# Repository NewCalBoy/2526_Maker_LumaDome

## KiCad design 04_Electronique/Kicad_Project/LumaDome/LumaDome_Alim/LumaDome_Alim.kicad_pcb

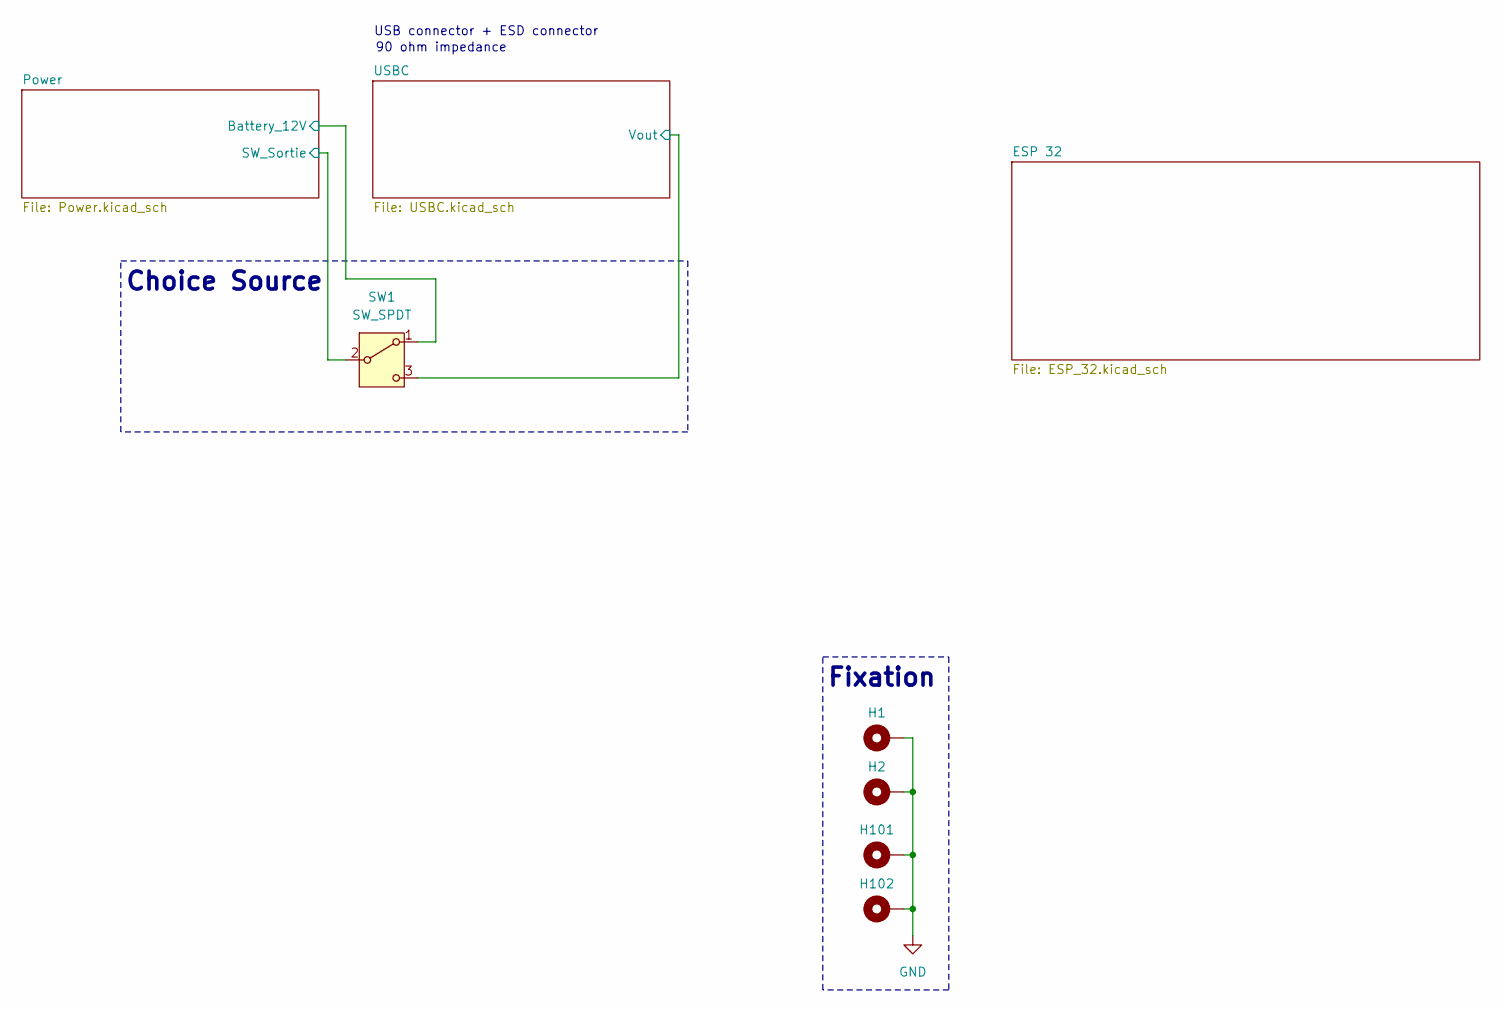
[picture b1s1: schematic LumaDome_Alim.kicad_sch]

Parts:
H1, H2, H101, H102: MountingHole_Pad; MountingHole_2.2mm_M2_Pad_Via
SW1: SW_SPDT; B12AV

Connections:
+12V: SW1.1 (A); also elsewhere on the board
/Power/SW_Sortie: SW1.2 (B); also elsewhere on the board
/USBC/Vout: SW1.3 (C); also elsewhere on the board
GND: H1.1, H2.1, H101.1, H102.1; also elsewhere on the board

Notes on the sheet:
90 ohm impedance
USB connector + ESD connector
Fixation
Choice Source

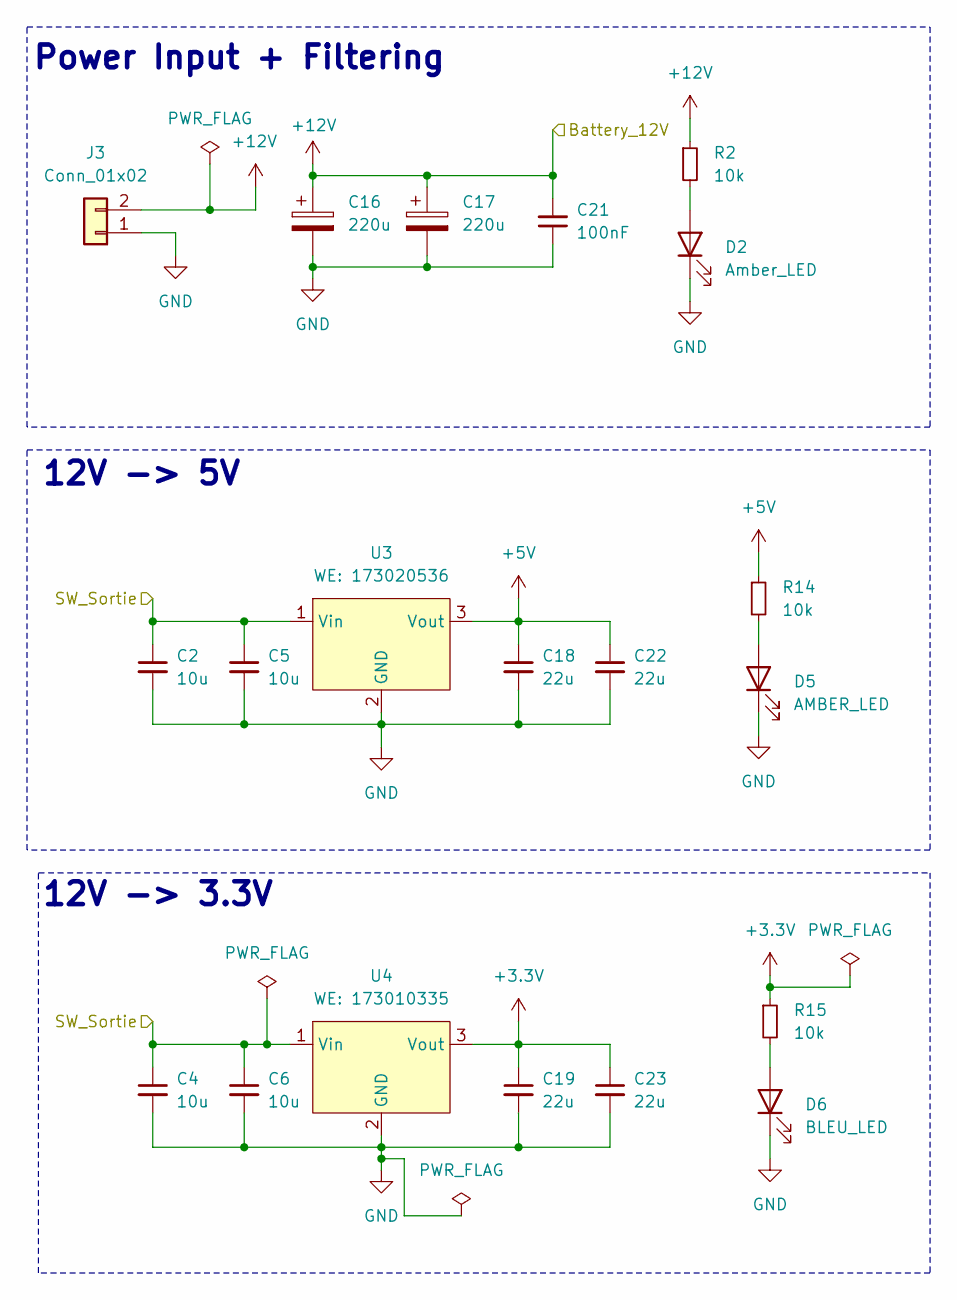
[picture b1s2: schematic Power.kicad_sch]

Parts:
C2, C4, C5, C6: 10u; C_2220_5750Metric; MPN 885012214001
C16, C17: 220u; CP_Elec_10x10.5; MPN 865060657012
C18, C19, C22, C23: 22u; C_2220_5750Metric; MPN 885012106031
C21: 100nF; C_0603_1608Metric
D2: Amber_LED; C_0603_1608Metric; MPN 150060AS55040
D5: AMBER_LED; C_0603_1608Metric; MPN 150060BS55040
D6: BLEU_LED; C_0603_1608Metric; MPN 150060BS55040
J3: Conn_01x02; AMASS_XT30UPB-F_1x02_P5.0mm_Vertical
R2, R14, R15: 10k; R_0603_1608Metric
U3: WE: 173020536; 173020536
U4: WE: 173010335; 173010335

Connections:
+3.3V: C19.1, C23.1, R15.1, U4.3 (Vout); also elsewhere on the board
+5V: C18.1, C22.1, R14.1, U3.3 (Vout); also elsewhere on the board
+12V: C16.1, C17.1, C21.2, J3.2, R2.1; also elsewhere on the board
/Power/SW_Sortie: C2.1, C4.1, C5.1, C6.1, U3.1 (Vin), U4.1 (Vin); also elsewhere on the board
GND: C2.2, C4.2, C5.2, C6.2, C16.2, C17.2, C18.2, C19.2, C21.1, C22.2, C23.2, D2.1 (K), D5.1 (K), D6.1 (K), J3.1, U3.2 (GND), U4.2 (GND); also elsewhere on the board
unnamed: D2.2 (A), R2.2
unnamed: D5.2 (A), R14.2
unnamed: D6.2 (A), R15.2

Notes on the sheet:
12V -> 5V
Power Input + Filtering
12V -> 3.3V

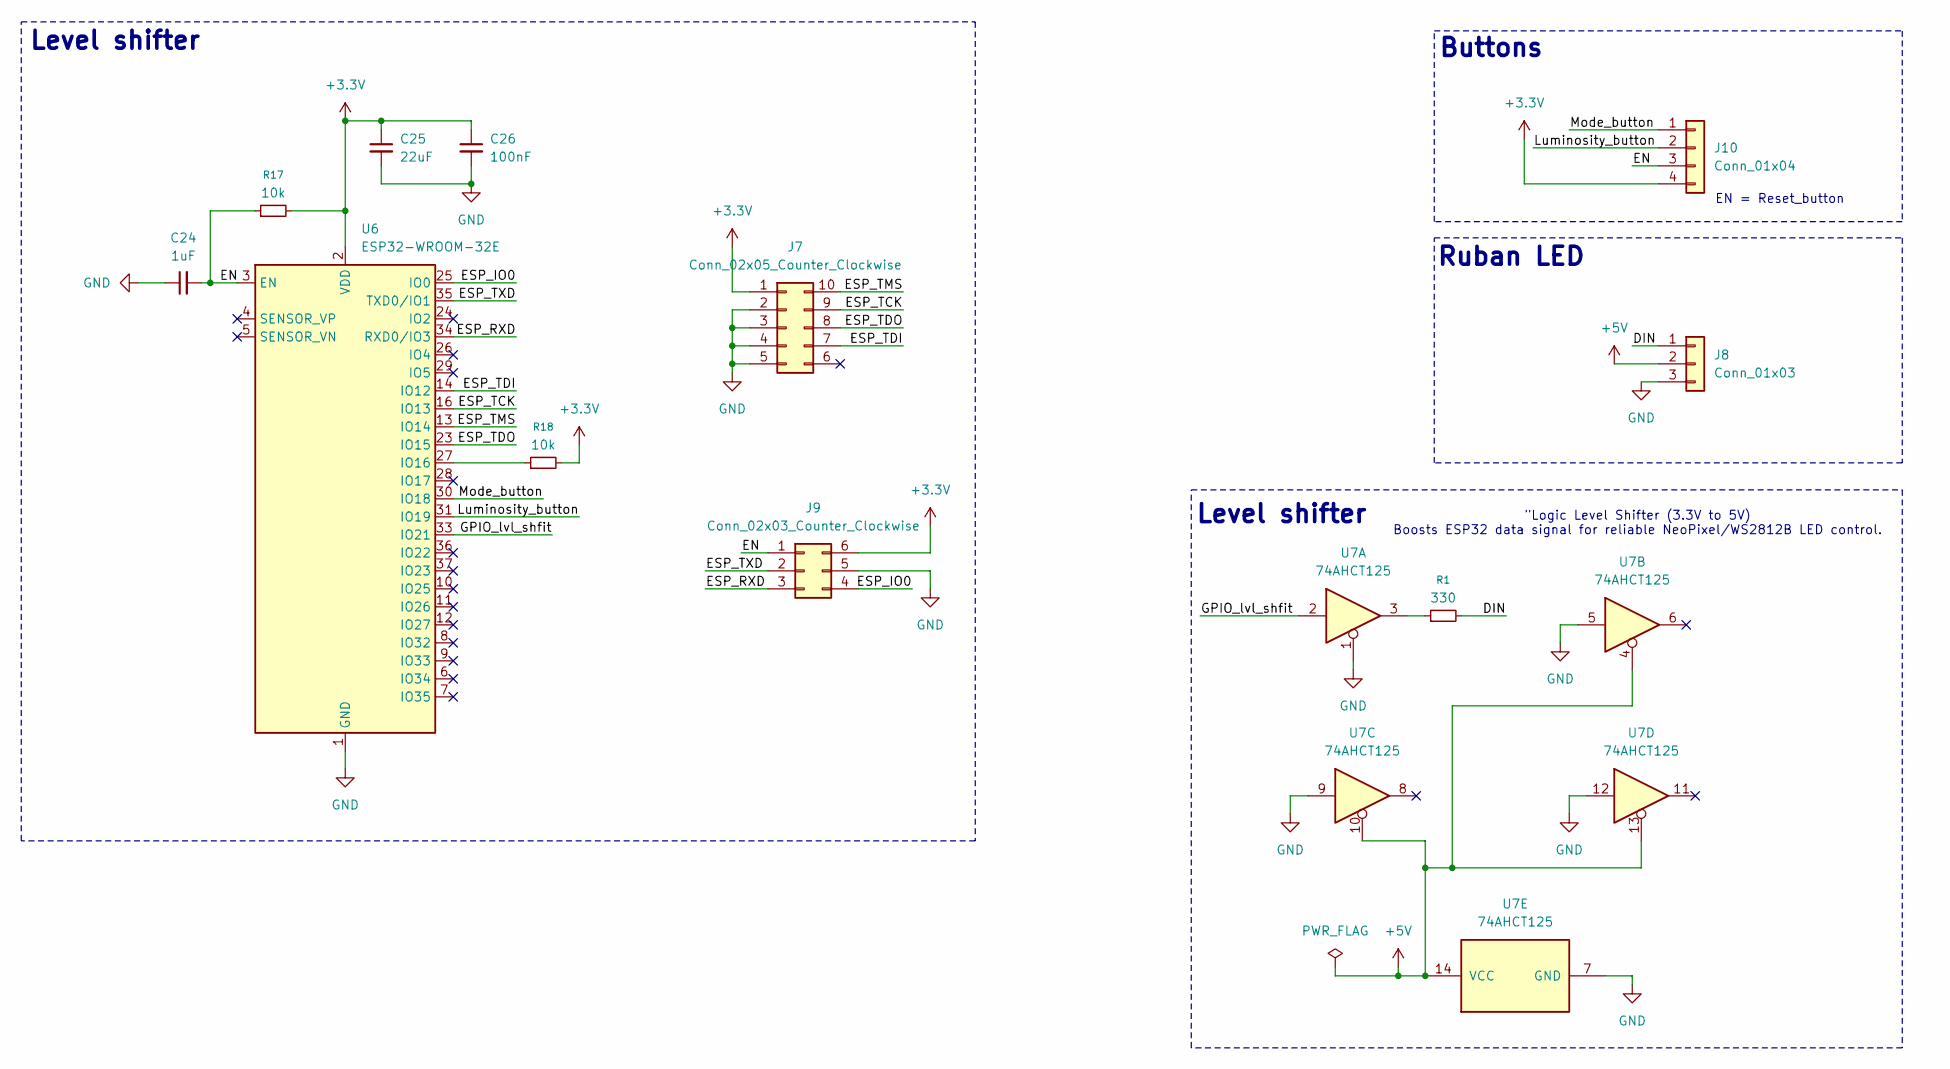
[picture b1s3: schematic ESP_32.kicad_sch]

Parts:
C24: 1uF; C_0603_1608Metric
C25: 22uF; C_2220_5750Metric
C26: 100nF; C_0603_1608Metric
J7: Conn_02x05_Counter_Clockwise; PinHeader_2x05_P1.27mm_Vertical_SMD
J8: Conn_01x03; JST_XH_B3B-XH-A_1x03_P2.50mm_Vertical
J9: Conn_02x03_Counter_Clockwise; PinHeader_2x03_P1.27mm_Vertical_SMD
J10: Conn_01x04; PinHeader_1x04_P2.54mm_Vertical_SMD_Pin1Left
R1: 330; R_0603_1608Metric
R17, R18: 10k; R_0603_1608Metric
U6: ESP32-WROOM-32E
U7: 74AHCT125; SOIC-14_3.9x8.7mm_P1.27mm

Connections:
+3.3V: C25.1, C26.1, J7.1, J9.6, J10.4, R17.2, R18.2, U6.2 (VDD); also elsewhere on the board
+5V: J8.2, U7.4, U7.10, U7.13, U7.14 (VCC); also elsewhere on the board
/ESP 32/DIN: J8.1, R1.2
/ESP 32/EN: C24.2, J9.1, J10.3, R17.1, U6.3 (EN)
/ESP 32/ESP_IO0: J9.4, U6.25 (IO0)
/ESP 32/ESP_RXD: J9.3, U6.34 (RXD0/IO3)
/ESP 32/ESP_TCK: J7.9, U6.16 (IO13)
/ESP 32/ESP_TDI: J7.7, U6.14 (IO12)
/ESP 32/ESP_TDO: J7.8, U6.23 (IO15)
/ESP 32/ESP_TMS: J7.10, U6.13 (IO14)
/ESP 32/ESP_TXD: J9.2, U6.35 (TXD0/IO1)
/ESP 32/GPIO_lvl_shfit: U6.33 (IO21), U7.2
/ESP 32/Luminosity_button: J10.2, U6.31 (IO19)
/ESP 32/Mode_button: J10.1, U6.30 (IO18)
GND: C24.1, C25.2, C26.2, J7.2, J7.3, J7.4, J7.5, J8.3, J9.5, U6.1 (GND), U6.15 (GND), U6.38 (GND), U6.39 (GND), U7.1, U7.5, U7.7 (GND), U7.9, U7.12; also elsewhere on the board
unnamed: R1.1, U7.3
unnamed: R18.1, U6.27 (IO16)

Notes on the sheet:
EN = Reset_button
Ruban LED
"Logic Level Shifter (3.3V to 5V) Boosts ESP32 data signal for reliable NeoPixel/WS2812B LED control.
Level shifter
Buttons

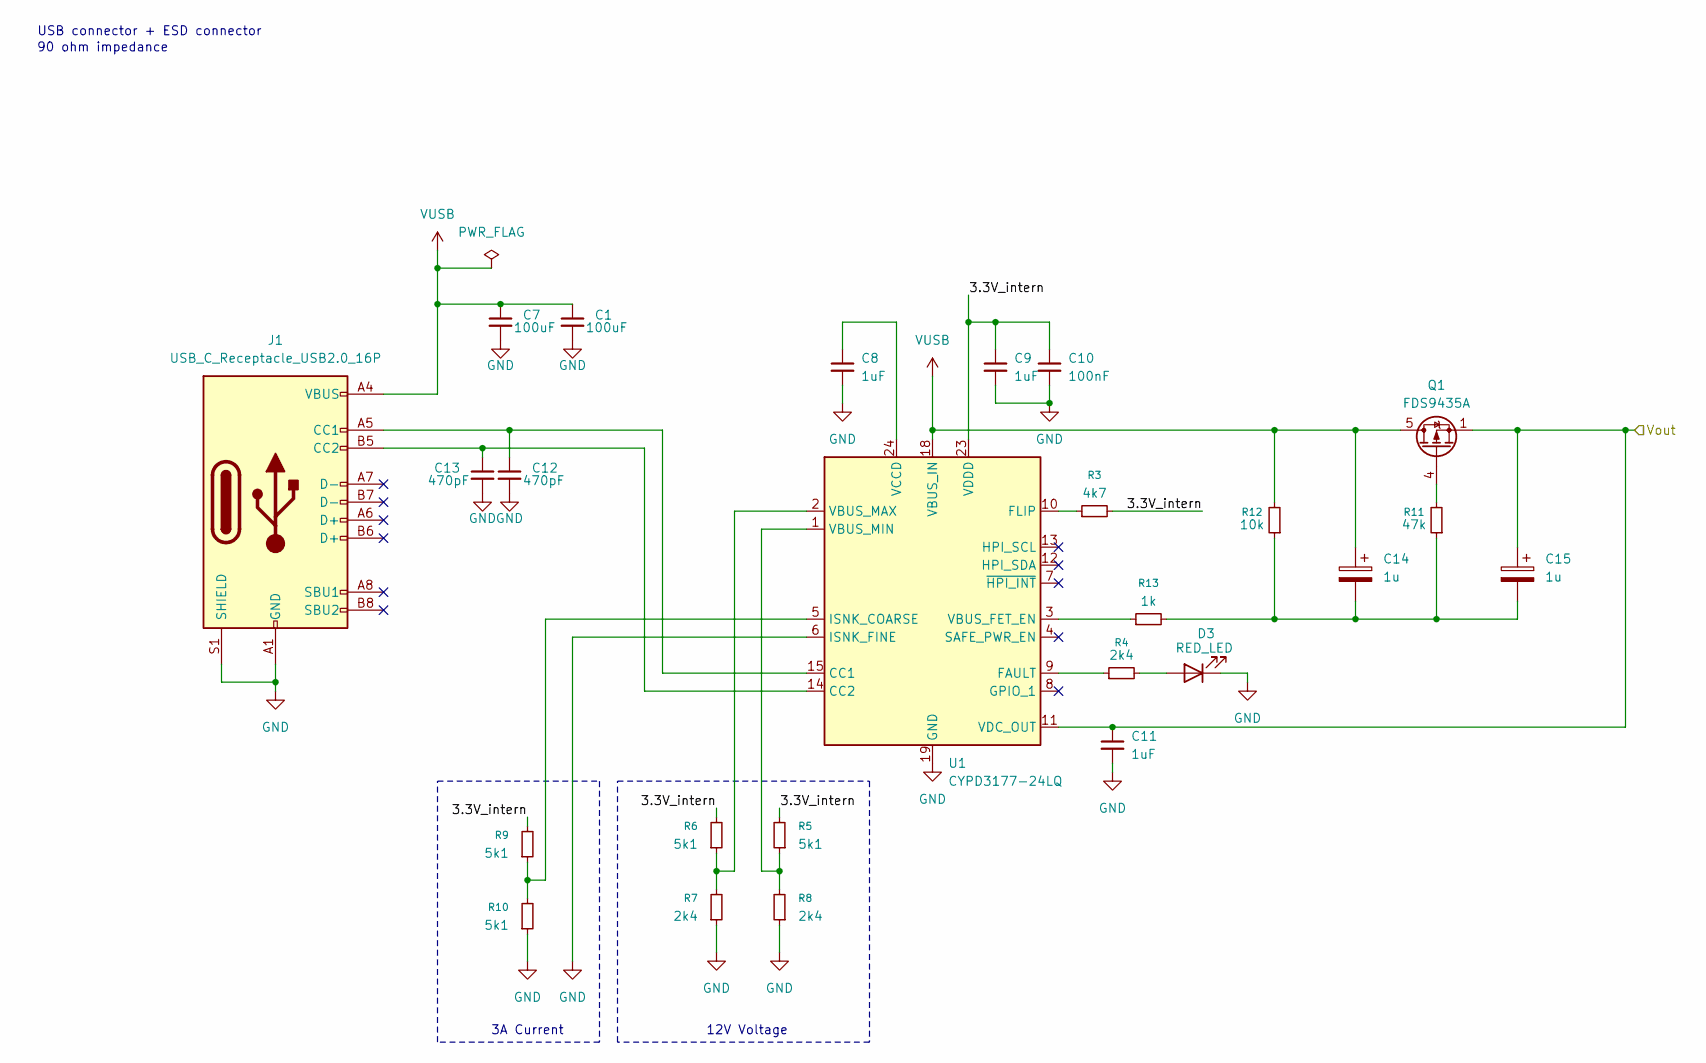
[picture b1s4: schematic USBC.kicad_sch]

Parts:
C1, C7: 100uF; C_0603_1608Metric
C8, C9, C11: 1uF; C_0603_1608Metric
C10: 100nF; C_0603_1608Metric
C12, C13: 470pF; C_0603_1608Metric
C14, C15: 1u; CP_Elec_5x5.4; MPN 865230342002
D3: RED_LED; C_0603_1608Metric; MPN 150060BS55040
J1: USB_C_Receptacle_USB2.0_16P; USB_C_Receptacle_GCT_USB4105-xx-A_16P_TopMnt_Horizontal
Q1: FDS9435A; SOIC-8_3.9x4.9mm_P1.27mm
R3: 4k7; R_0603_1608Metric
R4, R7, R8: 2k4; R_0603_1608Metric
R5, R6, R9, R10: 5k1; R_0603_1608Metric
R11: 47k; R_0603_1608Metric
R12: 10k; R_0603_1608Metric
R13: 1k; R_0603_1608Metric
U1: CYPD3177-24LQ; QFN-24-1EP_4x4mm_P0.5mm_EP2.75x2.75mm; MPN CYPD3177-24LQXQ

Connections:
/USBC/3.3V_intern: C9.1, C10.1, R3.2, R5.2, R6.2, R9.2, U1.23 (VDDD)
/USBC/Vout: C11.1, C15.1, Q1.1 (S), Q1.2 (S), Q1.3 (S), U1.11 (VDC_OUT); also elsewhere on the board
GND: C1.2, C7.2, C8.2, C9.2, C10.2, C11.2, C12.2, C13.2, D3.1 (K), J1.A1 (GND), J1.A12 (GND), J1.B1 (GND), J1.B12 (GND), J1.S1 (SHIELD), R7.1, R8.1, R10.1, U1.6 (ISNK_FINE), U1.19 (GND), U1.22 (GND), U1.25 (GND); also elsewhere on the board
unnamed: C14.2, C15.2, R11.1, R12.1, R13.2
unnamed: D3.2 (A), R4.2
unnamed: C12.1, J1.A5 (CC1), U1.15 (CC1)
unnamed: C13.1, J1.B5 (CC2), U1.14 (CC2)
unnamed: Q1.4 (G), R11.2
unnamed: R4.1, U1.9 (FAULT)
unnamed: R3.1, U1.10 (FLIP)
unnamed: R9.1, R10.2, U1.5 (ISNK_COARSE)
unnamed: R13.1, U1.3 (VBUS_FET_EN)
unnamed: R6.1, R7.2, U1.2 (VBUS_MAX)
unnamed: R5.1, R8.2, U1.1 (VBUS_MIN)
unnamed: C8.1, U1.24 (VCCD)
VUSB: C1.1, C7.1, C14.1, J1.A4 (VBUS), J1.A9 (VBUS), J1.B4 (VBUS), J1.B9 (VBUS), Q1.5 (D), Q1.6 (D), Q1.7 (D), Q1.8 (D), R12.2, U1.18 (VBUS_IN)

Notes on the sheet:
90 ohm impedance
12V Voltage
USB connector + ESD connector
3A Current

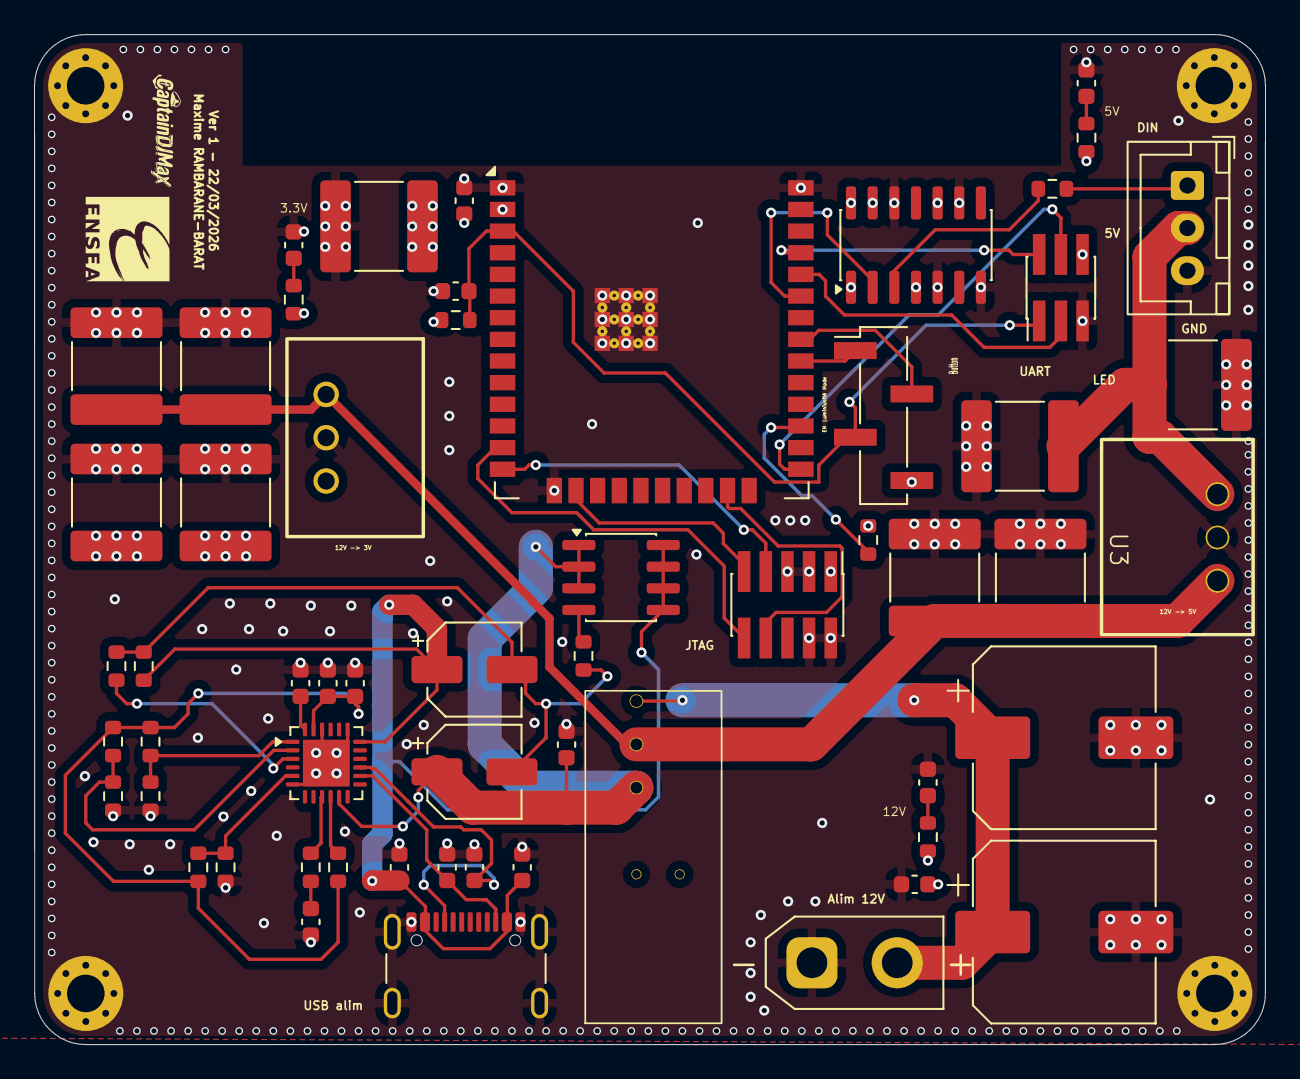
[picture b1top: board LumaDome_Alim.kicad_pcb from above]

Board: 4 copper layers, 72.2 x 59.3 mm, 62 parts (0 on the bottom side), 37 nets.

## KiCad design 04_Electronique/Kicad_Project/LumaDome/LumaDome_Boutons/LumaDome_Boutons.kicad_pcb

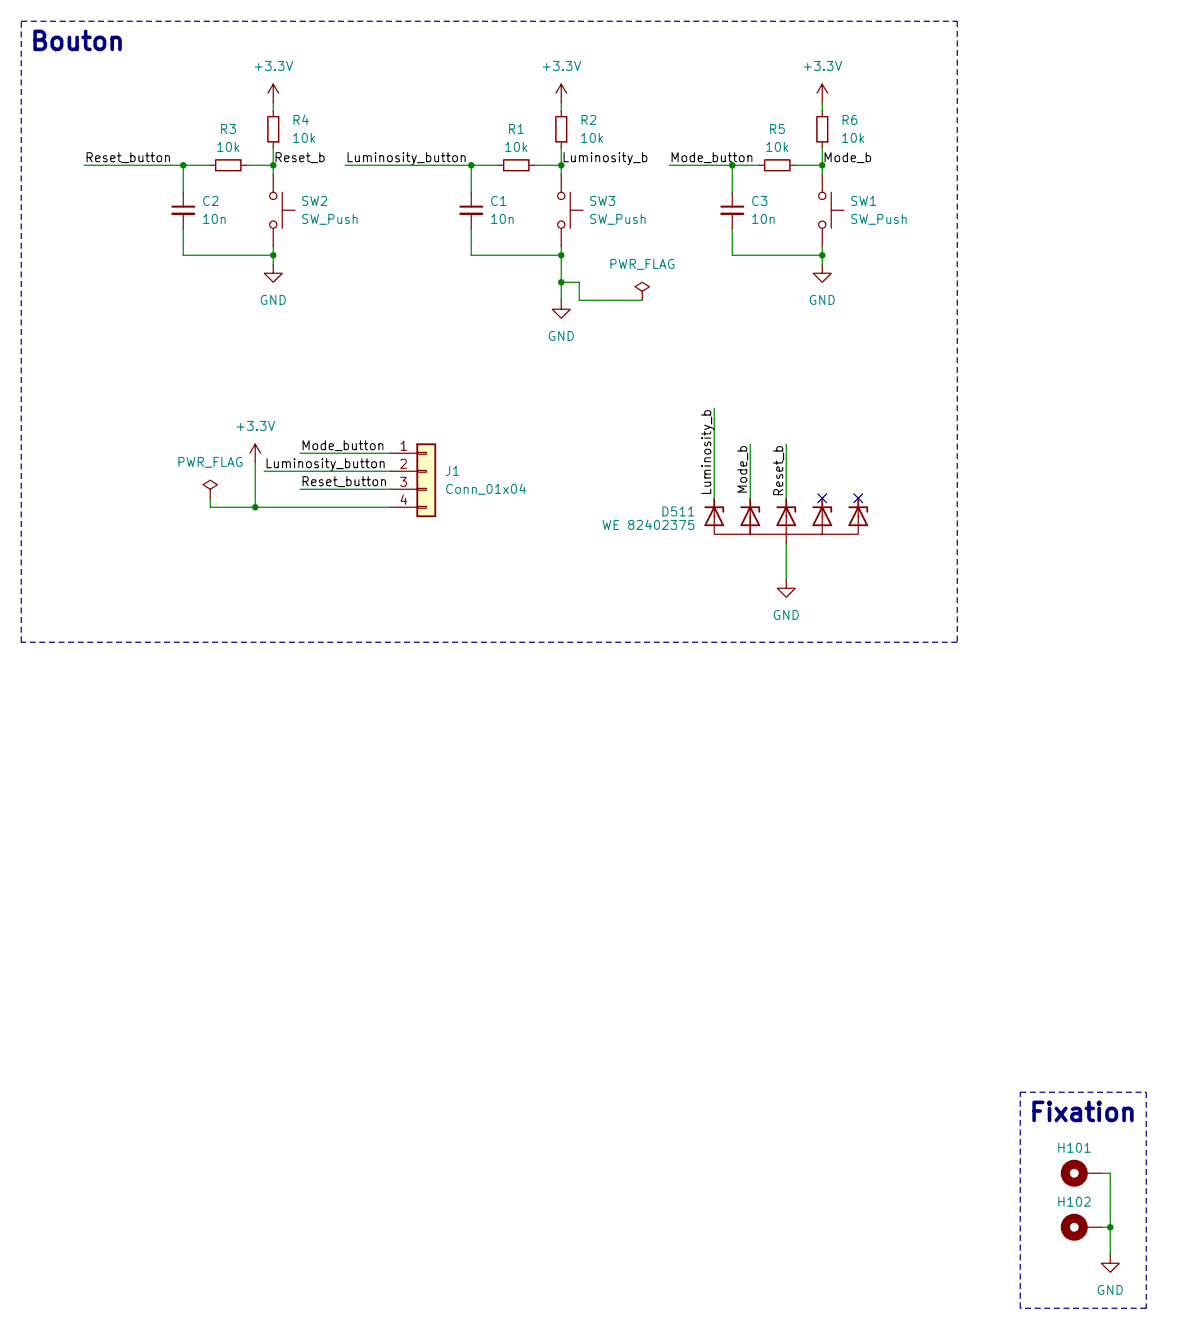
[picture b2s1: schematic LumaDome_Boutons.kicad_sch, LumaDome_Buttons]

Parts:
C1, C2, C3: 10n; C_0402_1005Metric; MPN WE 885012205050
D511: WE 82402375; SC70-6L; MPN WE 82402375
H101, H102: MountingHole_Pad; MountingHole_2.2mm_M2_Pad_Via
J1: Conn_01x04; PinHeader_1x04_P1.27mm_Vertical
R1, R2, R3, R4, R5, R6: 10k; R_0402_1005Metric
SW1, SW2, SW3: SW_Push; SW_PUSH_6mm

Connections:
+3.3V: J1.4, R2.2, R4.2, R6.2
/Luminosity_b: D511.6 (I/O), R1.2, R2.1, SW3.1
/Luminosity_button: C1.1, J1.2, R1.1
/Mode_b: D511.5 (I/O), R5.2, R6.1, SW1.1
/Mode_button: C3.1, J1.1, R5.1
/Reset_b: D511.4 (I/O), R3.2, R4.1, SW2.1
/Reset_button: C2.1, J1.3, R3.1
GND: C1.2, C2.2, C3.2, D511.2 (GND), H101.1, H102.1, SW1.2, SW2.2, SW3.2

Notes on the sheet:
Bouton
Fixation

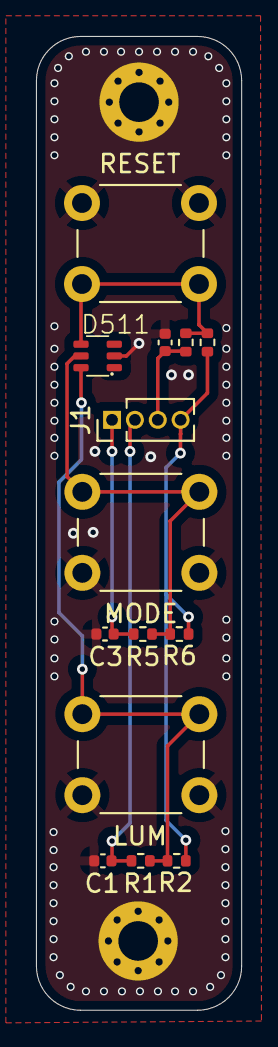
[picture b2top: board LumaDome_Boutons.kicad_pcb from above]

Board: 2 copper layers, 11.4 x 54.1 mm, 16 parts (0 on the bottom side), 8 nets.

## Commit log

2026-03-23 Finalisation PCB 02
2026-03-23 finalisation PCB
2026-05-03 Create 05_Code
